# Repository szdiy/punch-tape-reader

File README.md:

# punch-tape-reader

1. /hardware - hardware design files
2. paper_tape_reader.ino - Arduino program for reading paper tape to keyboard

Refs: todo

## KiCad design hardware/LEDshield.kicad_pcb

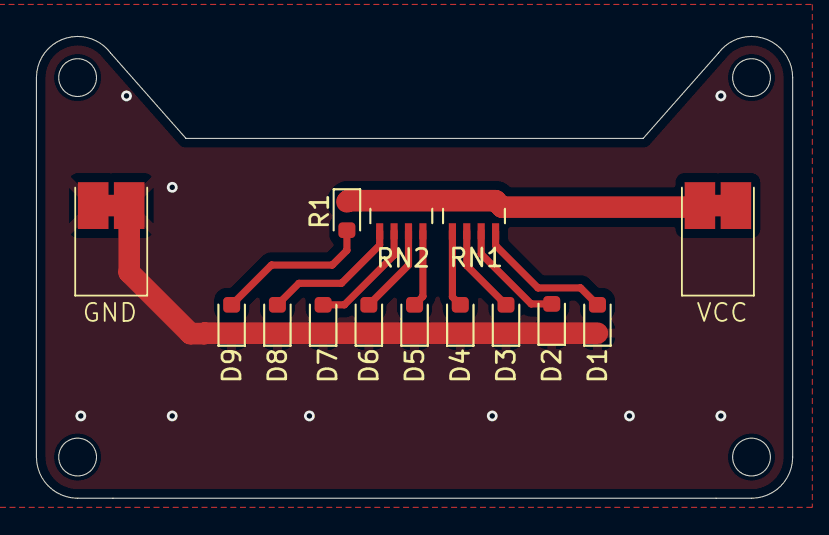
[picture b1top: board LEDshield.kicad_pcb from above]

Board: 2 copper layers, 42.0 x 25.7 mm, 18 parts (0 on the bottom side), 11 nets.

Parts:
D1, D2, D3, D4, D5, D6, D7, D8, D9: LED; LED_0603_1608Metric
H1, H2, H3, H4: MountingHole; MountingHole_2.1mm
J1: Conn_VCC; 2pin
J2: Conn_GND; 2pin
R1: 330R; LED_0603_1608Metric
RN1, RN2: 330R; R_Array_Concave_4x0603

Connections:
GND: D1.1 (K), D2.1 (K), D3.1 (K), D4.1 (K), D5.1 (K), D6.1 (K), D7.1 (K), D8.1 (K), D9.1 (K), J2.1, J2.2
unnamed: D1.2 (A), RN1.4 (R4.1)
unnamed: D2.2 (A), RN1.3 (R3.1)
unnamed: D3.2 (A), RN1.2 (R2.1)
unnamed: D4.2 (A), RN1.1 (R1.1)
unnamed: D5.2 (A), RN2.4 (R4.1)
unnamed: D6.2 (A), RN2.3 (R3.1)
unnamed: D7.2 (A), RN2.2 (R2.1)
unnamed: D8.2 (A), RN2.1 (R1.1)
unnamed: D9.2 (A), R1.2
VCC: J1.1, J1.2, R1.1, RN1.5 (R4.2), RN1.6 (R3.2), RN1.7 (R2.2), RN1.8 (R1.2), RN2.5 (R4.2), RN2.6 (R3.2), RN2.7 (R2.2), RN2.8 (R1.2)

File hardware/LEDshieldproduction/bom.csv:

Designator,Footprint,Quantity,Value,LCSC Part #
"D1, D2, D3, D4, D5, D6, D7, D8, D9",603,9,LED,
J1,BC-12-2P170,1,Conn_VCC,
J2,BC-12-2P170,1,Conn_GND,
R1,603,1,330R,
"RN1, RN2",R_Array_Concave_4x0603,2,330R,

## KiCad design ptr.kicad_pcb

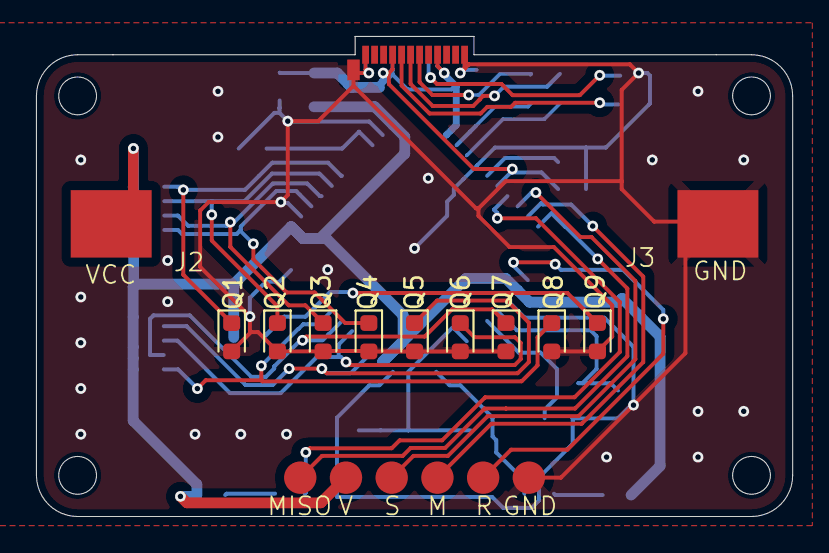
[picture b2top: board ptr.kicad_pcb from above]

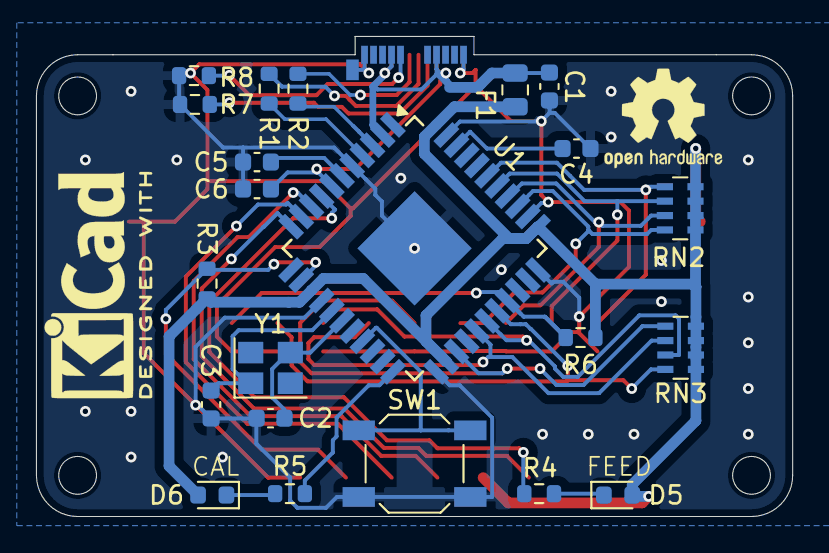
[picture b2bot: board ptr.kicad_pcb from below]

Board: 2 copper layers, 42.0 x 26.7 mm, 39 parts (22 on the bottom side), 31 nets.

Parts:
C1, C5, C6: 1uF; C_0603_1608Metric
C2, C3: 22pF; C_0603_1608Metric
C4: 0.1uF; C_0603_1608Metric
D5: FEED LED GREEN; LED_0603_1608Metric
D6: CAL LED YELLOW; LED_0603_1608Metric
F1: 500mA; Fuse_0805_2012Metric
H1, H2, H3, H4: MountingHole; MountingHole_2.1mm
J1: ICSP; testPoints 6pin
J2: Conn_VCC; 1pin
J3: Conn_GND; 1pin
P1: USB_C_Plug; USB_C_Plug_Molex_105444
Q1, Q2, Q3, Q4, Q5, Q6, Q7, Q8, Q9: BPW40; LED_0603_1608Metric
R1, R2: 22R; R_0603_1608Metric
R3: 10K; R_0603_1608Metric
R4, R5: 330R; R_0603_1608Metric
R6: 4K7; R_0603_1608Metric
R7: 5K1; R_0603_1608Metric
R8: NC; R_0603_1608Metric
RN2, RN3: 4K7; R_Array_Concave_4x0603
SW1: SW_Push; SW_SPST_SKQG_WithStem
U1: ATmega32U4-M; TQFP-44-1EP_10x10mm_P0.8mm_EP4.5x4.5mm
Y1: 16M; Crystal_SMD_3225-4Pin_3.2x2.5mm

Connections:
/D+: R1.2, U1.4 (D+)
/D-: R2.2, U1.3 (D-)
/DATA0: Q1.1 (C), RN2.1 (R1.1), U1.39 (PF4)
/DATA1: Q2.1 (C), RN2.2 (R2.1), U1.38 (PF5)
/DATA2: Q3.1 (C), RN2.3 (R3.1), U1.37 (PF6)
/DATA3: Q5.1 (C), RN3.1 (R1.1), U1.25 (PD4)
/DATA4: Q6.1 (C), RN3.2 (R2.1), U1.27 (PD7)
/DATA5: Q7.1 (C), RN3.3 (R3.1), U1.28 (PB4)
/DATA6: Q8.1 (C), RN3.4 (R4.1), U1.29 (PB5)
/DATA7: Q9.1 (C), R6.2, U1.30 (PB6)
/DN: P1.A7 (D-), R2.1
/DP: P1.A6 (D+), R1.1
/FEED: Q4.1 (C), RN2.4 (R4.1), U1.36 (PF7)
/MISO: J1.1, U1.11 (PB3)
/MOSI: J1.4, U1.10 (PB2)
/RESET: J1.5, R3.2, U1.13 (~RESET)
/SCK: J1.3, U1.9 (PB1)
GND: C1.2, C2.1, C3.1, C4.1, C5.1, C6.2, J1.6, J3.1, P1.A1 (GND), P1.A12 (GND), P1.B1 (GND), P1.B12 (GND), P1.S1 (SHIELD), Q1.2 (E), Q2.2 (E), Q3.2 (E), Q4.2 (E), Q5.2 (E), Q6.2 (E), Q7.2 (E), Q8.2 (E), Q9.2 (E), R7.2, R8.2, SW1.2, U1.5 (UGND), U1.15 (GND), U1.23 (GND), U1.33 (~HWB/PE2), U1.35 (GND), U1.43 (GND), U1.45 (GND)
unnamed: D5.1 (K), R4.2
unnamed: D6.1 (K), R5.2
unnamed: P1.A5 (CC), R7.1
unnamed: P1.B5 (VCONN), R8.1
unnamed: C4.2, U1.42 (AREF)
unnamed: R4.1, U1.8 (PB0)
unnamed: SW1.1, U1.19 (PD1)
unnamed: R5.1, U1.22 (PD5)
unnamed: C5.2, U1.6 (UCAP)
unnamed: C2.2, U1.17 (XTAL1), Y1.3
unnamed: C3.2, U1.16 (XTAL2), Y1.1
VBUS: C1.1, C6.1, F1.1, P1.A4 (VBUS), P1.A9 (VBUS), P1.B4 (VBUS), P1.B9 (VBUS), U1.2 (UVCC), U1.7 (VBUS)
VCC: D5.2 (A), D6.2 (A), F1.2, J1.2, J2.1, R3.1, R6.1, RN2.5 (R4.2), RN2.6 (R3.2), RN2.7 (R2.2), RN2.8 (R1.2), RN3.5 (R4.2), RN3.6 (R3.2), RN3.7 (R2.2), RN3.8 (R1.2), U1.14 (VCC), U1.24 (AVCC), U1.34 (VCC), U1.44 (AVCC)

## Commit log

2024-11-01 copy from https://www.e-basteln.de/file/papertape/Paper_Tape_Reader.ino
2024-11-03 add danfei v1103
2024-11-03 format
2024-11-04 add lixin edtion
2024-11-14 init code from danfei
2024-11-14 use the keyboard version
2024-11-14 change dir and update readme
